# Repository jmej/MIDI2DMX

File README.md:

# MIDI2DMX

## Teensy driven DJ light and LED control via MIDI

### This project was developed to facilitate curriculum at Portland Community College for the Music and Sonic Arts department

MIDI2DMX provides a simple way to get total control over a wide variety of lights - using existing music software (Ableton Live, Logic, Bitwig, Garage Band, Pro Tools etc), as well as hardware midi sequencers like the Akai MPC series, the Elektron Octatrack, Alesis MMT-8, etc. It allows for easy interfacing with programming environments like Pure Data, MaxMSP, and Processing.

This makes it easy to sequence lights for live music performances, do algorithmic light programming, map lights using sound analysis, data from the internet, or sensor data etc.

It unlocks cheap DJ lights turning them into flexible and expressive tools/instruments.

I designed a PCB to make the circuit easy to build, and have assembled quite a number of them with students in my interactivity courses at Portland Community College. There is no wiring, it's a quick project and costs around $40 total.

Eagle files for the PCB are published here - but you can also order them (in multiples of 3) from OSHPark: https://oshpark.com/shared_projects/hyqqaC5r

This core of the design is a Teensy - with some solid and extremely fast DMX code from Paul Stoffregen. The result is much smoother and more reliable than any commercial solution I've used. Because of Paul's usb drivers - it can be programmed to be a USB midi device, so it will show up in any MIDI capable software on any OS. The code in this repo is setup to translate midi cc's into DMX channel values. (Mapping CC numbers directly to DMX channel numbers).

We've used the Teensy 3.2 for our builds - but an LC should also work https://www.pjrc.com/store/teensy32.html

The additional parts are available from mouser here: http://www.mouser.com/ProjectManager/ProjectDetail.aspx?AccessID=11855f0a7f

If you want a more detailed guide I've published this: http://www.instructables.com/id/MIDI2DMX/

###Other DMX solutions
It turns out that it's pretty hard to find a good, well supported, inexpensive DMX controller.

There are a lot of expensive DMX controllers with proprietary drivers. There are a lot of cheap DMX controllers with little or no documentation. (Although these days a lot of them are copied from the uDMX project). Some of them work intermittently, some work only on windows, and some work only with specific (unexciting) DMX control software.

The uDMX project http://www.anyma.ch/research/udmx/ is the only well documented open source option out there, but in my experience - it's not that good. It suffers from choppy framerates and frequent drop outs, and on top of that, all the units I tried became unresponsive fairly often in a variety of software applications. There is a fundamental design flaw: it relies on your computer to send DMX frames. If your computer is processing audio (from Pure Data or Max for instance) - you end up with pretty severe audio dropouts. Also your framerate suffers due to various computer and USB bus performance issues. By contrast - this code makes the Teensy handle sending all the DMX frames, it just keeps the current channel values in an array that gets updated as midi data gets sent. So only value changes get transmitted via USB and the Teensy does the work of sending continual, fast frames whether they get updated or not. There is no pause in the Arduino loop - it sends out frames as fast as it can resulting in super smooth curves and animations.

##PD:
In the PD folder you'll find a few example patches for Pure Data (http://puredata.info/). While you can control lights using this board from anything that can send midi - PD offers a lot more options and flexibility than most other midi software. I run patches like these on a Raspberry Pi for live use.

DMX_color_presets.pd shows how to translate RGB and HSV color values into messages you can send to your lights. Google has a nice color picker tool. https://www.google.com/webhp?sourceid=chrome-instant&ion=1&espv=2&ie=UTF-8#q=color%20picker

hsv2rbg.pd is an abstraction that the other patches rely on. All of these pd patches need to be put in the same folder to work correctly.

DMX_color_organ.pd has a simple midi mapping using Scriabin's pitch-color associations. https://en.wikipedia.org/wiki/Clavier_%C3%A0_lumi%C3%A8res

This makes any DMX light playable from a midi keyboard or midi sequencer like Ableton Live, Logic, Bitwig - as well as hardware sequencers like MPCs and Octatracks. This is my preferred method for programming custom light shows for live PA's.

Finally DMX_audio_analysis.pd demonstrates pitch and amplitude tracking and translation into light color and intensity using pd.

##Hardware Midi:
The hardware midi part of this board is untested - and the code doesn't support it yet. But it probably works, it just needs some arduino code to handle midi input on the Teensy's second Serial RX line.

##Future Dev:
Aside from implementing hardware midi - the plan is to setup some color and envelope control on the Teensy to replace some of work I'm currently doing with PD. An enclosure is also in progress.

##Schematic Errata:
Even though the schematic shows a PC110 optocoupler - it is actually wired and laid out for a Sharp PC900V optocoupler. The schmetic is correct - as long as you use a PC900V and not a PC110. It would need to be changed for a different optocoupler.

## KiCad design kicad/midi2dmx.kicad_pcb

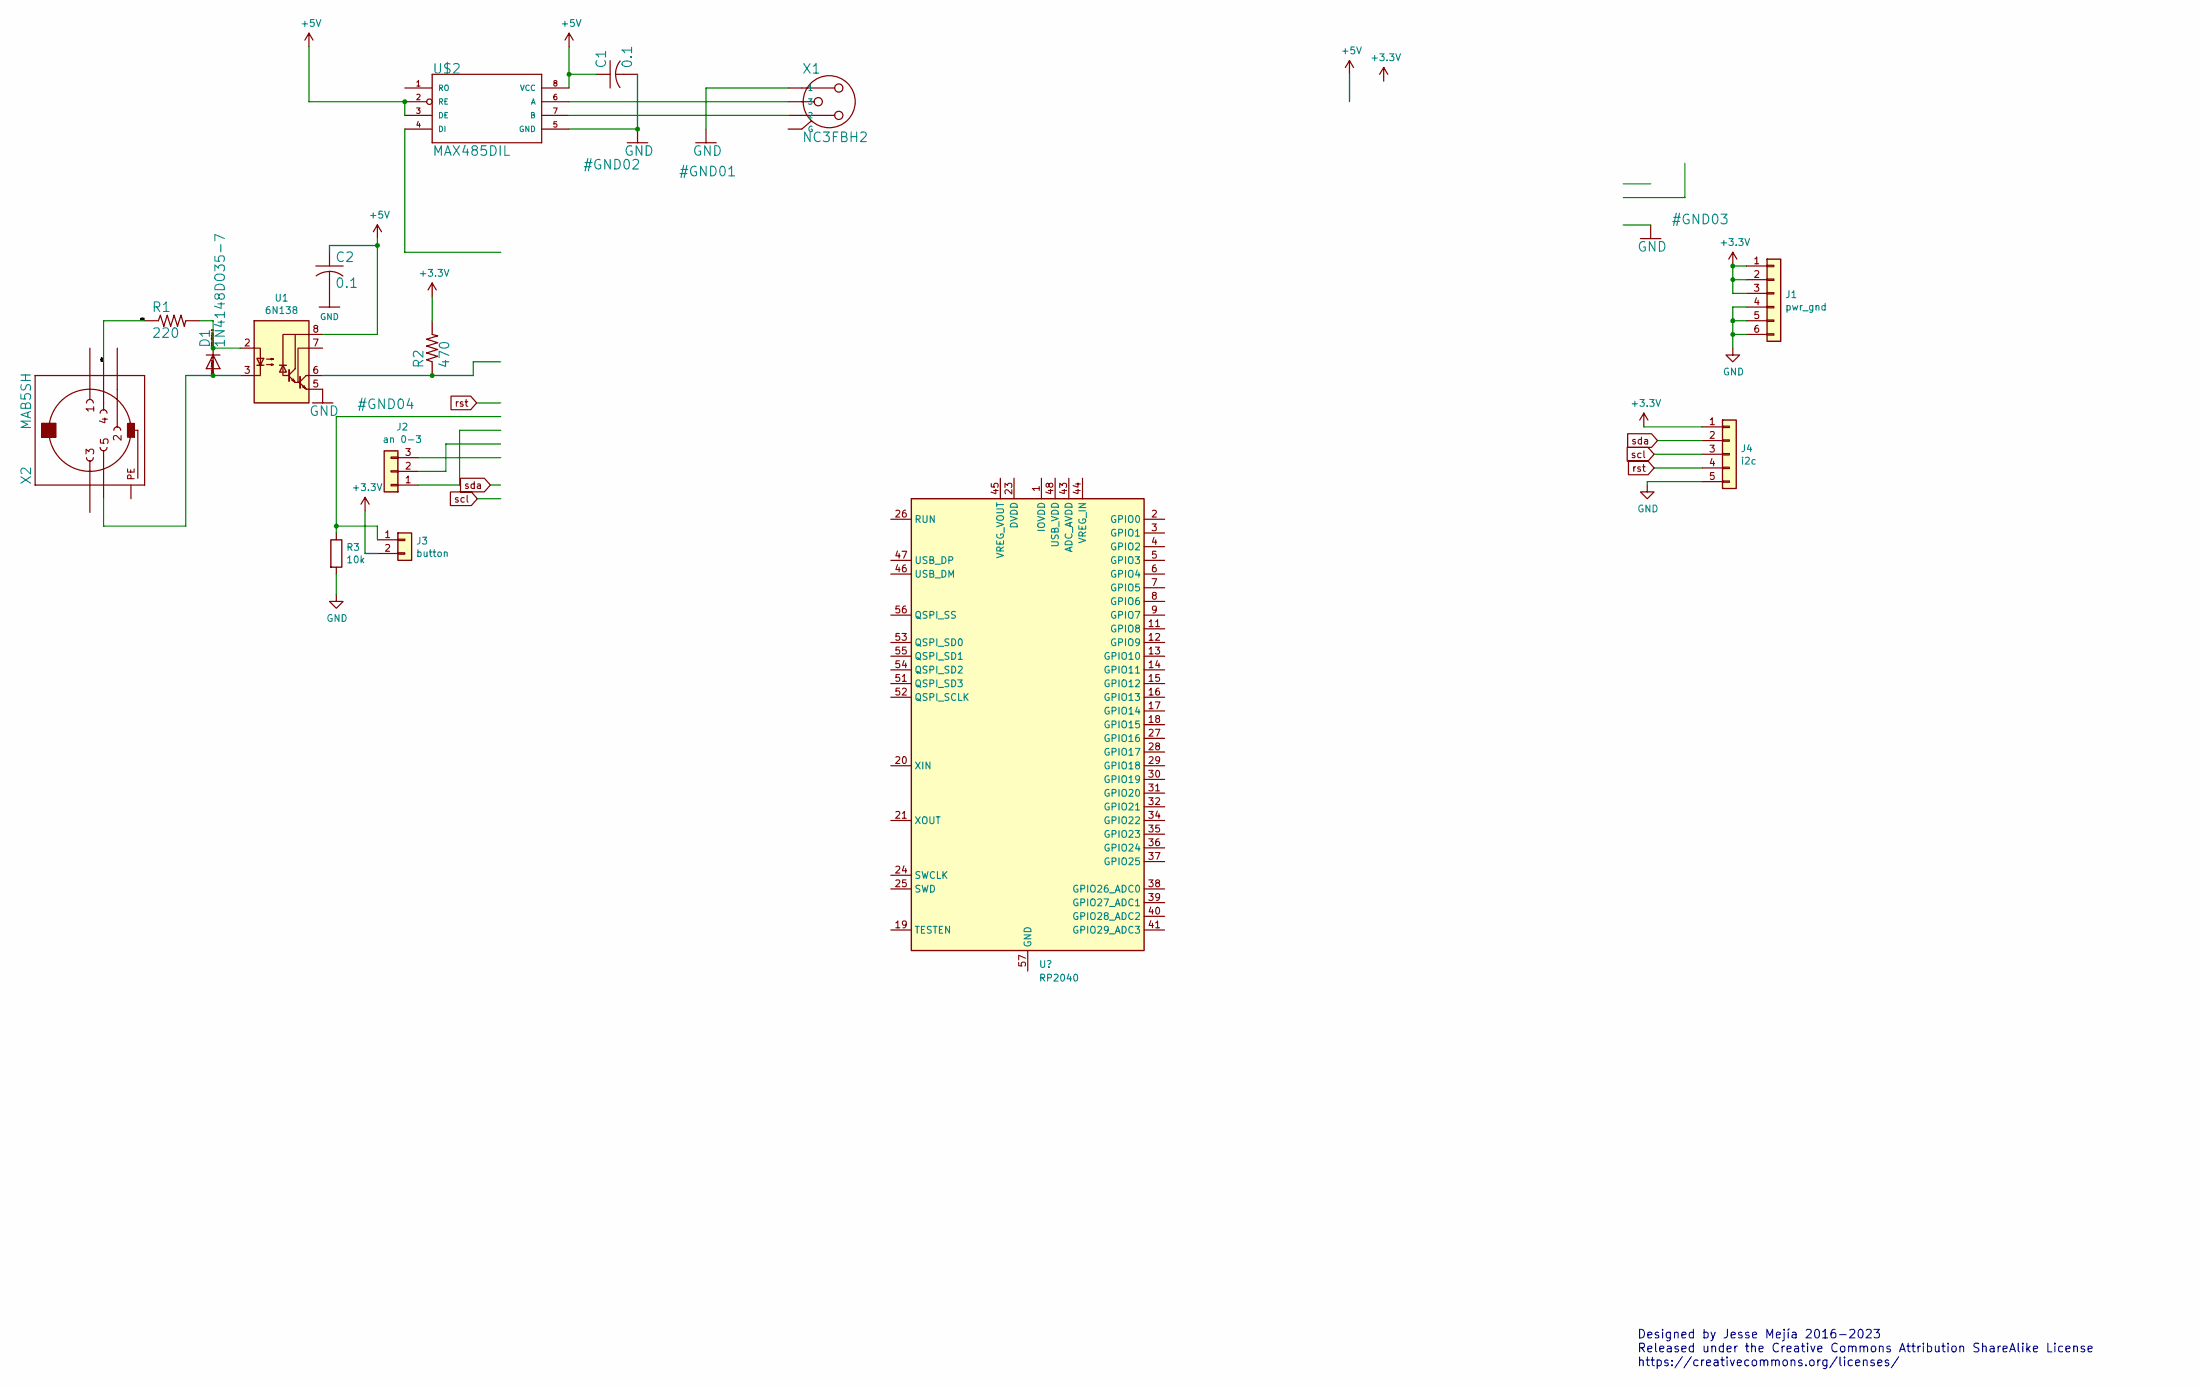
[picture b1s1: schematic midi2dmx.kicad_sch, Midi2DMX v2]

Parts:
C1, C2: 0.1; C025-024X044
D1: 1N4148DO35-7; DO35-7
J1: pwr_gnd; Pins_1x06_2.54mm_TH_SWD
J2: an 0-3; Pins_1x03_2.54mm_TH
J3: button; Pins_1x02_2.54mm_TH
J4: i2c; Pins_1x05_2.54mm_TH
R1: 220; R_Axial_DIN0207_L6.3mm_D2.5mm_P7.62mm_Horizontal
R2: 470; R_Axial_DIN0207_L6.3mm_D2.5mm_P7.62mm_Horizontal
R3: 10k; R_Axial_DIN0207_L6.3mm_D2.5mm_P7.62mm_Horizontal
U1: 6N138; DIP-8pin_TH
U$2: MAX485DIL; DIP-8pin_TH
X1: NC3FBH2
X2: MAB5SH

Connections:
+3V3: J1.1, J1.2, J1.3, J3.2, J4.1, R2.2; also elsewhere on the board
+5V: C1.1, C2.1, U1.8 (VCC), U$2.2 (RE), U$2.3 (DE), U$2.8 (VCC); also elsewhere on the board
/N$6: R1.1, X2.4
GND: C1.2, C2.2, J1.4, J1.5, J1.6, J4.5, R3.2, U1.5 (GND), U$2.5 (GND), X1.1; also elsewhere on the board
unnamed: D1.A, U1.3 (C2), X2.5
unnamed: D1.C, R1.2, U1.2 (C1)
unnamed 6: J2.1; also elsewhere on the board
unnamed 7: J2.2; also elsewhere on the board
unnamed 8: J2.3; also elsewhere on the board
unnamed 9: J3.1, R3.1; also elsewhere on the board
unnamed 10: R2.1, U1.6 (VO2); also elsewhere on the board
unnamed 15: U$2.4 (DI); also elsewhere on the board
unnamed: U$2.6 (A), X1.3
unnamed: U$2.7 (B), X1.2
PE: X2.PE, X2.PE@ (PE)
rst: J4.4; also elsewhere on the board
scl: J4.3; also elsewhere on the board
sda: J4.2; also elsewhere on the board

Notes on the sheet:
Designed by Jesse Mejía 2016-2023 Released under the Creative Commons Attribution ShareAlike License https://creativecommons.org/licenses/

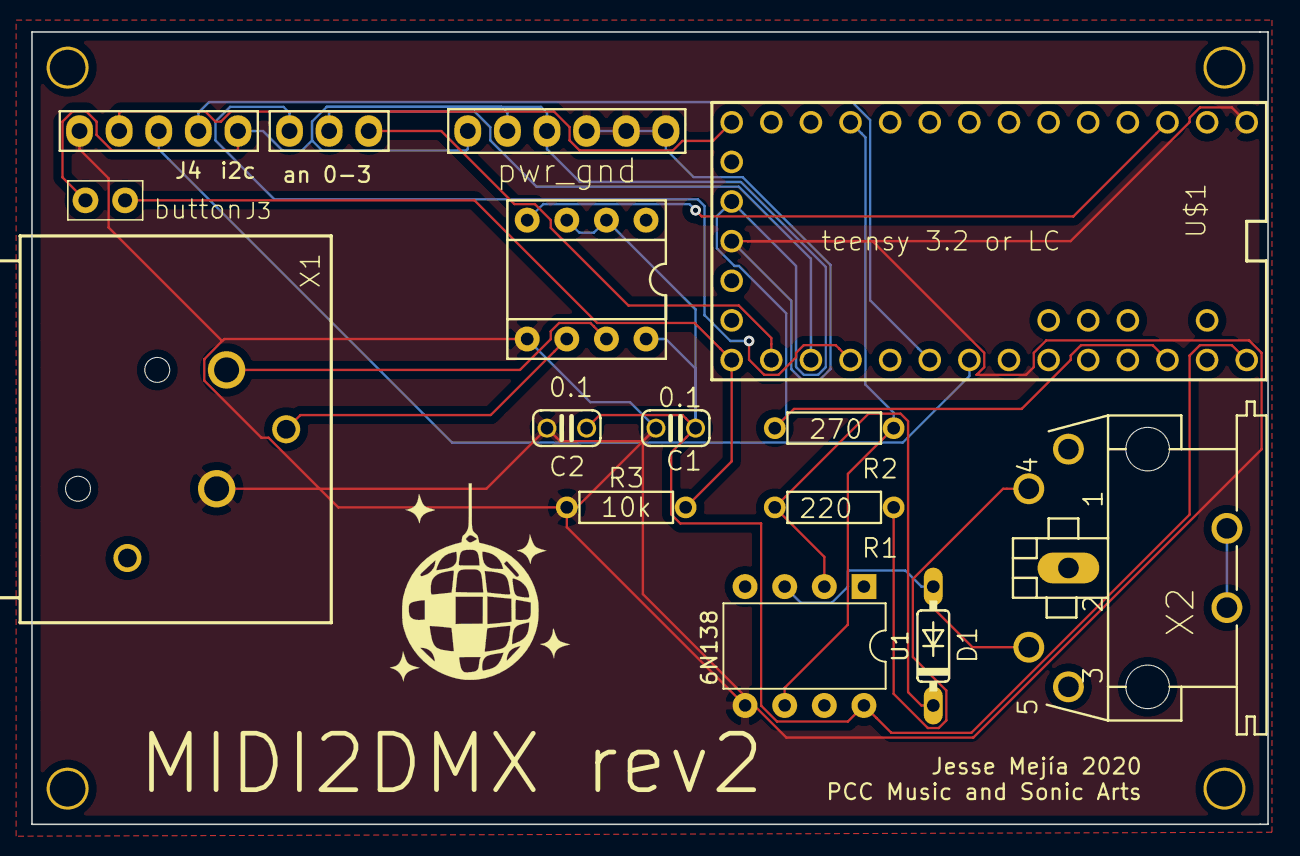
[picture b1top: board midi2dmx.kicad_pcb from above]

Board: 2 copper layers, 79.2 x 50.8 mm, 19 parts (0 on the bottom side), 18 nets.

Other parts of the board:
M?: 2-56 Screw; MountingHole_2-56
M?#2, M?#3, M?#4: 2-56 Screw; MountingHole_2-56
U$1: TEENSY_3.1-3.2_ALL_PINS; TEENSY_3.0-3.2&LC_ALL_PINS

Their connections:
+3V3: U$1.3.3V, U$1.3.3V1; also elsewhere on the board
+5V: U$1.VIN; also elsewhere on the board
GND: U$1.GND, U$1.GND1; also elsewhere on the board
unnamed 6: U$1.14/A0; also elsewhere on the board
unnamed 7: U$1.15/A1; also elsewhere on the board
unnamed 8: U$1.16/A2; also elsewhere on the board
unnamed 9: U$1.13; also elsewhere on the board
unnamed 10: U$1.9; also elsewhere on the board
unnamed 15: U$1.1; also elsewhere on the board
rst: U$1.12; also elsewhere on the board
scl: U$1.19/A5; also elsewhere on the board
sda: U$1.18/A4; also elsewhere on the board

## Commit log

2016-11-27 Minor fix in DMX code, only needed for larger # of DMX channels
2017-09-05 adds simple standalone demo
2018-06-30 untested midi note funcionality
2019-03-12 initial conversion to kicad
2019-03-12 rev2 schematic work
2019-03-20 remove tiny labels
2019-06-12 adds support for 512 dmx channels
2019-06-12 Revert "adds support for 512 dmx channels"
    This reverts commit ce72b4abcd339d6fd9302ca5fe8feac92f709eb6.
2019-10-16 removing test file
2019-10-16 adds back channel expansion
2019-10-16 wip for note mode
2019-12-21 adds lasercut case plans in progress, removes broken NoteIn stuff
2020-01-15 fixes channel update again
2020-01-22 some board work and variable name change
2020-01-29 updates schematic for v2
2020-02-17 rev2 pcb almost ready for fab
2022-05-20 Change the device name to 'MIDI2DMX'
    Added names.c file to change the name that identifies the device in the OS
2022-12-06 changes example from RGBW to RGB
2022-12-06 cleanup of fade example
2023-03-02 swapped teensy with rp2030
2023-03-02 schematic in progress for 2040
2024-05-18 adds max example
2025-02-12 adds color organ example
2025-03-05 rp2040 port and new pcb rev wip
2025-03-17 dmx implementation working, colors and timing wip
2025-03-17 fixes color bug that was disguised as a timing bug
2025-03-17 started pcb based on the rp2040 dev board
2025-03-18 working
2025-03-18 pcb wip
2025-04-01 channelized color organ
2026-04-29 kicad wip
